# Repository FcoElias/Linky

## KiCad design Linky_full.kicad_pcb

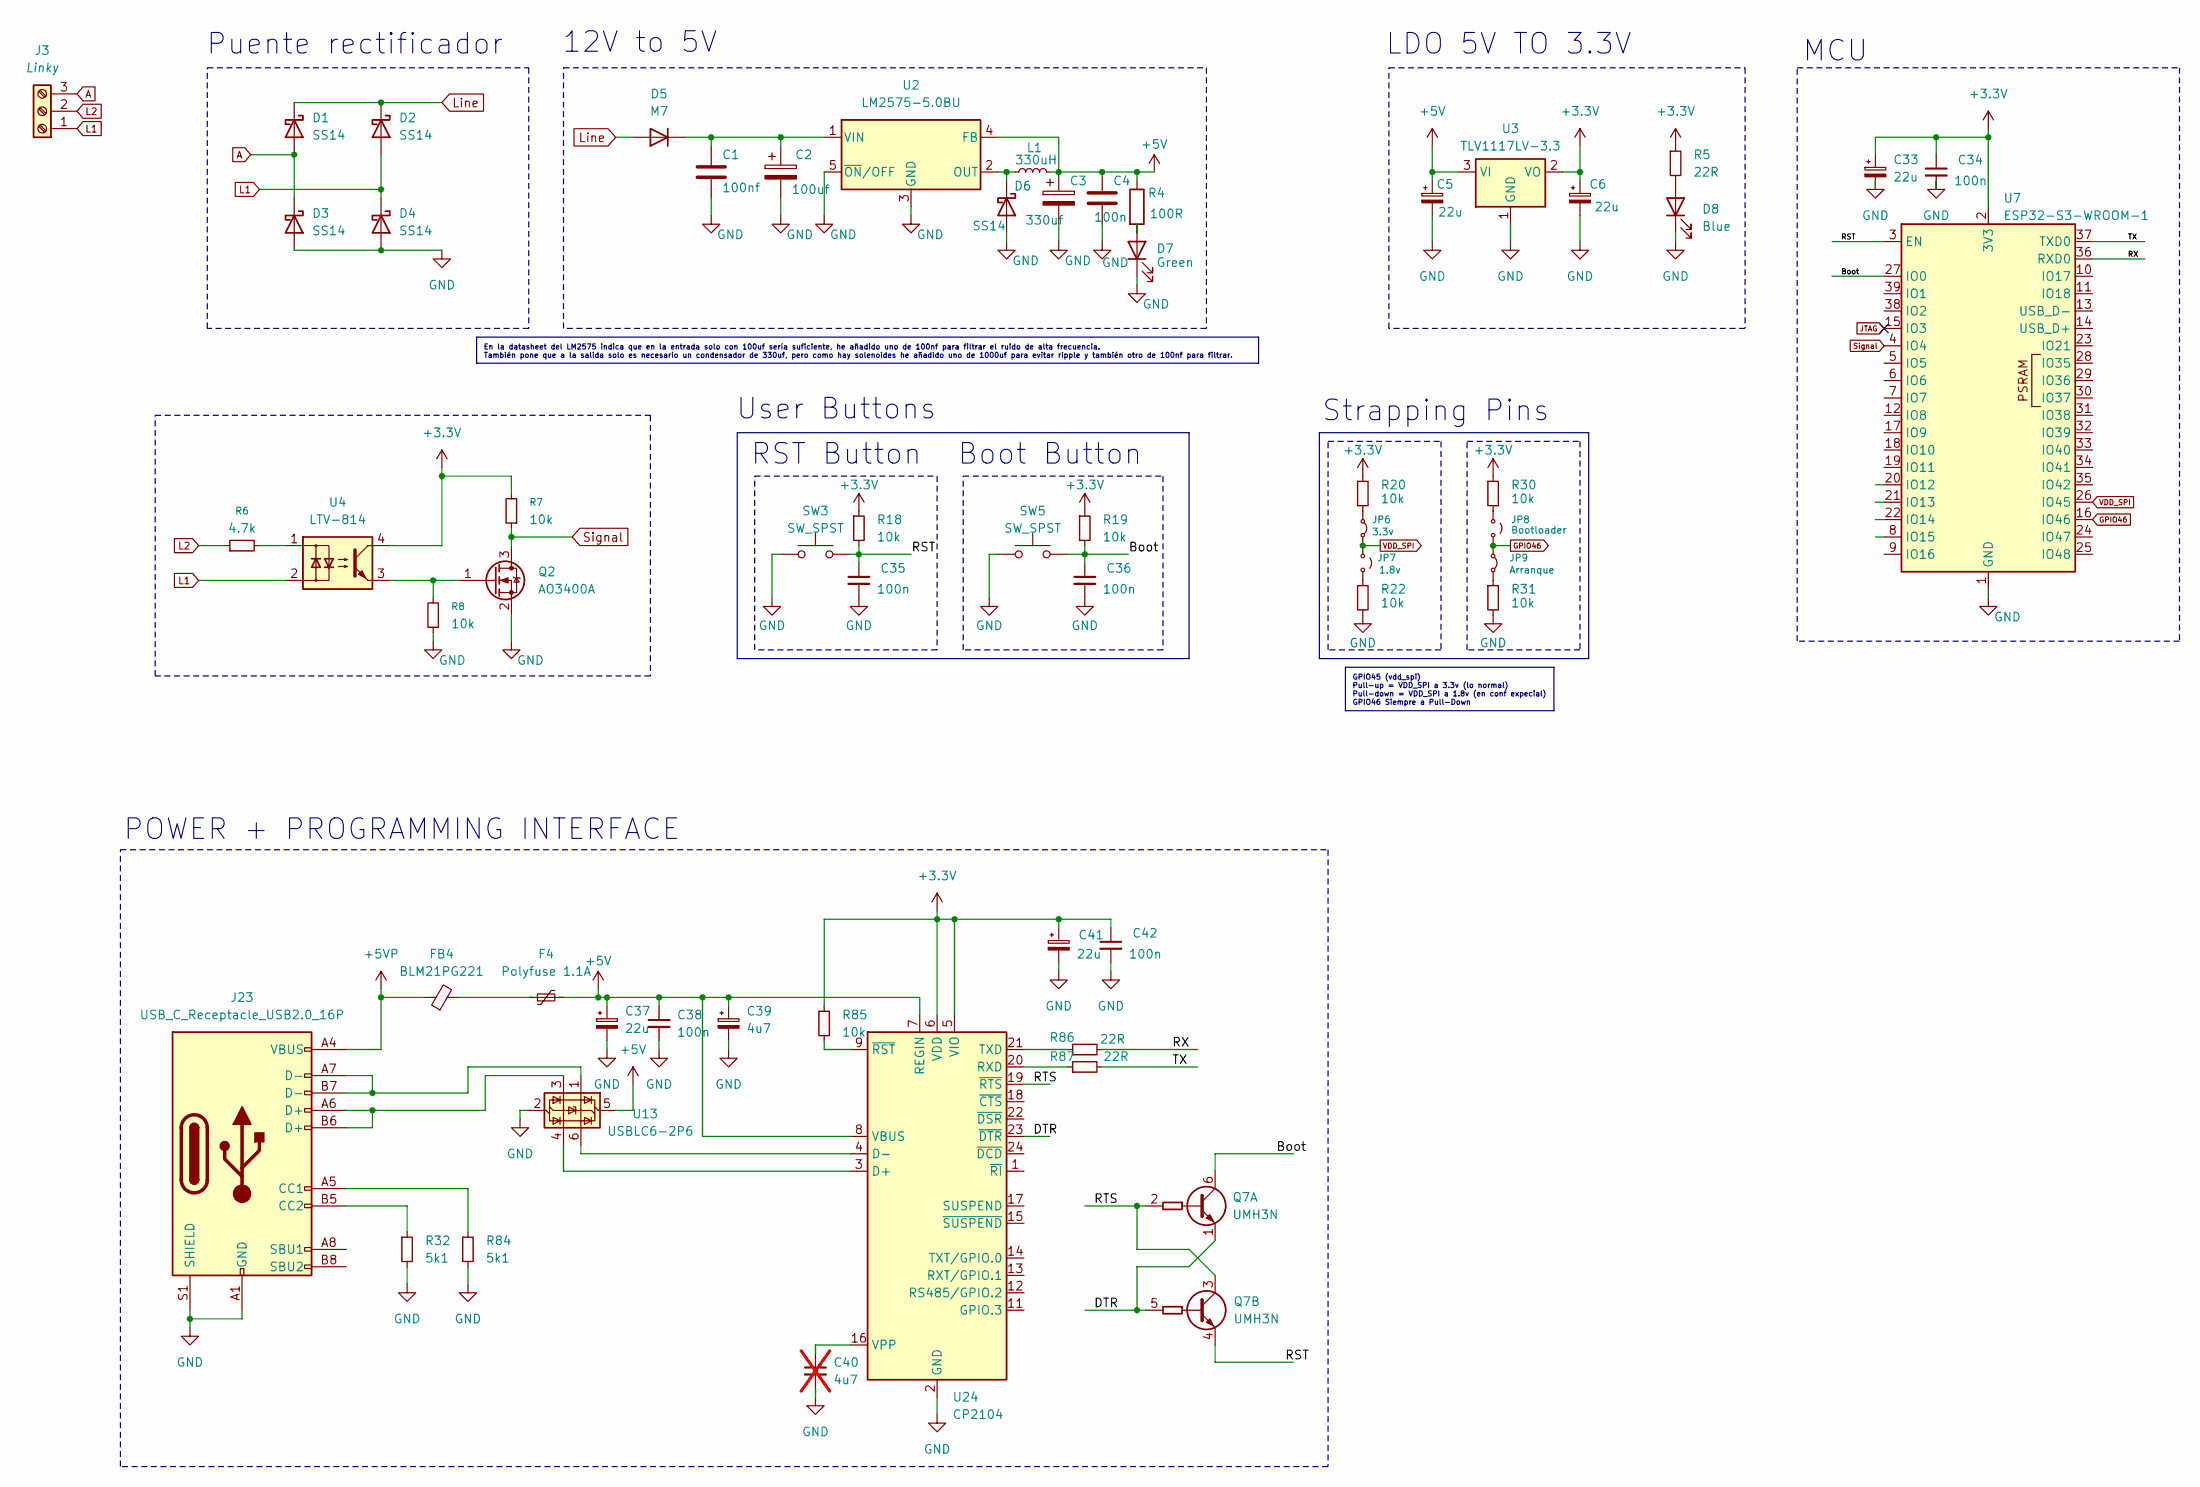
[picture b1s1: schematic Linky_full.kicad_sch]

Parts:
C1: 100nf; C_0805_2012Metric
C2: 100uf; C_Elec_4x5.4
C3: 330uf; C_Elec_10x10.2
C4, C34, C35, C36, C38, C42: 100n; C_0805_2012Metric
C5, C6, C33, C37, C41: 22u; C_Elec_5x5.4
C39: 4u7; C_Elec_4x5.4
C40: 4u7; C_0805_2012Metric_Pad1.18x1.45mm_HandSolder; not fitted
D1, D2, D3, D4, D6: SS14; D_SMA
D5: M7; D_SMA
D7: Green; LED_0603_1608Metric
D8: Blue; LED_0603_1608Metric
F4: Polyfuse 1.1A; Fuse_1206_3216Metric
FB4: BLM21PG221; L_0805_2012Metric
J3: Linky; TerminalBlock_bornier-3_P5.08mm
J23: USB_C_Receptacle_USB2.0_16P; USB_C_Receptacle_GCT_USB4110
JP6: 3.3v; PinHeader_1x02_P1.00mm_Vertical
JP7: 1.8v; PinHeader_1x02_P1.00mm_Vertical
JP8: Bootloader; PinHeader_1x02_P1.00mm_Vertical
JP9: Arranque; PinHeader_1x02_P1.00mm_Vertical
L1: 330uH; L_Pulse_PA4340
Q2: AO3400A; SOT-23
Q7: UMH3N; SOT-363_SC-70-6
R4: 100R; R_0805_2012Metric
R5, R86, R87: 22R; R_0805_2012Metric
R6: 4.7k; R_0805_2012Metric
R7, R8, R18, R19, R20, R22, R30, R31, R85: 10k; R_0805_2012Metric
R32, R84: 5k1; R_0805_2012Metric
SW3, SW5: SW_SPST; SW_Push_SPST_NO_Alps_SKRK
U2: LM2575-5.0BU; TO-263-5_TabPin3
U3: TLV1117LV-3.3; SOT-223-3_TabPin2
U4: LTV-814; DIP-4_W7.62mm
U7: ESP32-S3-WROOM-1
U13: USBLC6-2P6; SOT-23-6
U24: CP2104; QFN-24-1EP_4x4mm_P0.5mm_EP2.6x2.6mm

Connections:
+3.3V: C6.1, C33.1, C34.1, C41.1, C42.1, R5.1, R7.2, R18.1, R19.1, R20.1, R30.1, R85.1, U3.2 (VO), U4.4, U7.2 (3V3), U24.5 (VIO), U24.6 (VDD)
+5V: C3.1, C4.1, C5.1, C37.1, C38.1, C39.1, F4.2, L1.2, R4.1, U2.4 (FB), U3.3 (VI), U13.5 (VBUS), U24.7 (REGIN), U24.8 (VBUS)
+5VP: FB4.1, J23.A4 (VBUS), J23.A9 (VBUS), J23.B4 (VBUS), J23.B9 (VBUS)
/Boot: C36.1, Q7.6 (C1), R19.2, SW5.2, U7.27 (IO0)
/DTR: Q7.1 (E1), Q7.5 (B2), U24.23 (~DTR)
/RST: C35.1, Q7.4 (E2), R18.2, SW3.2, U7.3 (EN)
/RTS: Q7.2 (B1), Q7.3 (C2), U24.19 (~RTS)
/RX: R86.2, U7.36 (RXD0)
/TX: R87.2, U7.37 (TXD0)
A: D1.2 (A), D3.1 (K), J3.3
GND: C1.2, C2.2, C3.2, C4.2, C5.2, C6.2, C33.2, C34.2, C35.2, C36.2, C37.2, C38.2, C39.2, C40.2, C41.2, C42.2, D3.2 (A), D4.2 (A), D6.2 (A), D7.1 (K), D8.1 (K), J23.A1 (GND), J23.A12 (GND), J23.B1 (GND), J23.B12 (GND), J23.S1 (SHIELD), Q2.2 (S), R8.1, R22.2, R31.2, R32.2, R84.2, SW3.1, SW5.1, U2.3 (GND), U2.5 (~ON/OFF), U3.1 (GND), U7.1 (GND), U7.40 (GND), U7.41 (GND), U13.2 (GND), U24.2 (GND), U24.25 (GND)
GPIO46: JP8.2 (B), JP9.1 (A), U7.16 (IO46)
JTAG: U7.15 (IO3)
L1: D2.2 (A), D4.1 (K), J3.1, U4.2
L2: J3.2, R6.1
Line: D1.1 (K), D2.1 (K), D5.2 (A)
unnamed: C1.1, C2.1, D5.1 (K), U2.1 (VIN)
unnamed: D6.1 (K), L1.1, U2.2 (OUT)
unnamed: D7.2 (A), R4.2
unnamed: D8.2 (A), R5.2
unnamed: F4.1, FB4.2
unnamed: J23.A5 (CC1), R84.1
unnamed: J23.B5 (CC2), R32.1
unnamed: J23.A6 (D+), J23.B6 (D+), U13.3 (I/O2)
unnamed: J23.A7 (D-), J23.B7 (D-), U13.1 (I/O1)
unnamed: JP6.1 (A), R20.2
unnamed: JP7.2 (B), R22.1
unnamed: JP8.1 (A), R30.2
unnamed: JP9.2 (B), R31.1
unnamed: Q2.1 (G), R8.2, U4.3
unnamed: R6.2, U4.1
unnamed: U13.4 (I/O2), U24.3 (D+)
unnamed: U13.6 (I/O1), U24.4 (D-)
unnamed: R87.1, U24.20 (RXD)
unnamed: R86.1, U24.21 (TXD)
unnamed: C40.1, U24.16 (VPP)
unnamed: R85.2, U24.9 (~RST)
Signal: Q2.3 (D), R7.1, U7.4 (IO4)
VDD_SPI: JP6.2 (B), JP7.1 (A), U7.26 (IO45)

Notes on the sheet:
Boot Button
RST Button
Puente rectificador
12V to 5V
LDO 5V TO 3.3V
User Buttons
POWER + PROGRAMMING INTERFACE
MCU
Strapping Pins
GPIO45 (vdd_spi) Pull-up = VDD_SPI a 3.3v (lo normal) Pull-down = VDD_SPI a 1.8v (en conf expecial) GPIO46 Siempre a Pull-Down
En la datasheet del LM2575 indica que en la entrada solo con 100uf sería suficiente, he añadido uno de 100nf para filtrar el ruido de alta frecuencia. También pone que a la salida solo es necesario un condensador de 330uf, pero como hay solenoides he añadido uno de 1000uf para evitar ripple y tambi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

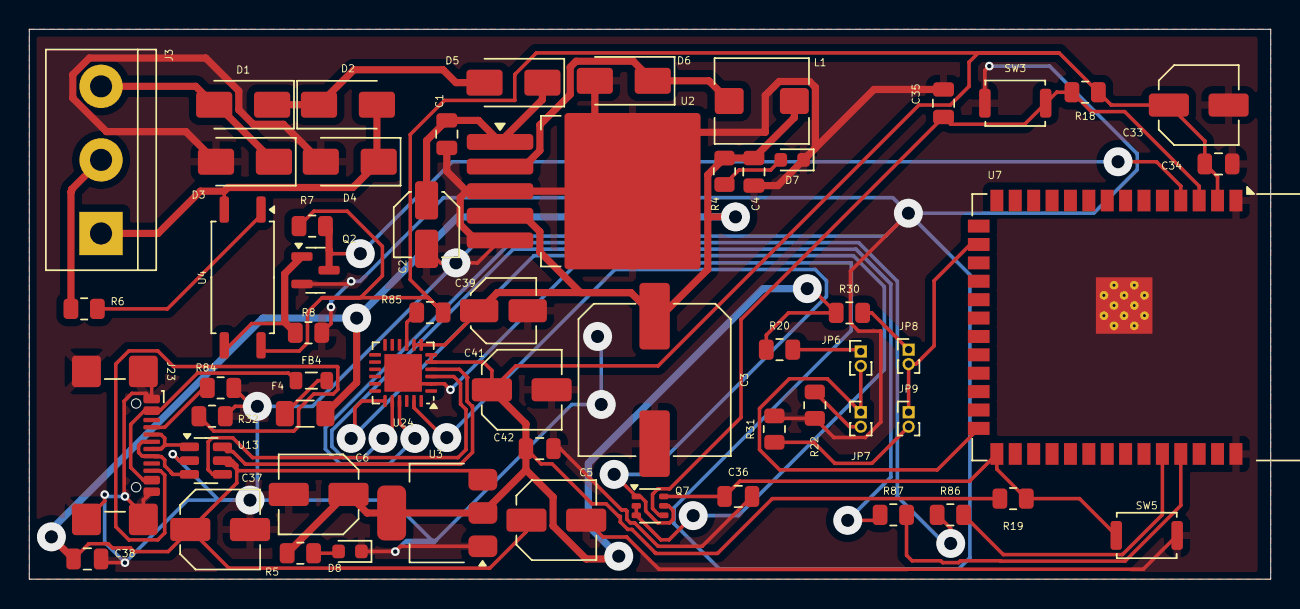
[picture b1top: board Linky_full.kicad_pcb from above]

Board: 2 copper layers, 85.7 x 38.0 mm, 58 parts (0 on the bottom side), 37 nets.

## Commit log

2025-05-06 Ficheros iniciales
2025-05-07 Placa ruteada y con GND
2025-05-08 Versión funcional con esquema completo, pcb y enrutado completo de pistas. Falta mejorar la posición y el tamaño de la pcb
2025-05-09 Versión compacta y ruteada terminada. Falta el silkscreen y verificar DRC
2025-05-09 Silkscreen terminado y versión mecanizable
